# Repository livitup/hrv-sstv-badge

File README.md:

# DEFCON SSTV Badge

An open-source SSTV (Slow Scan Television) badge designed for DEFCON and the broader badgelife community. This badge combines amateur radio, digital imaging, and social interaction into a wearable electronic art piece shaped like a Simpsons-style retro TV with rabbit ear antennas.

## Project Overview

The DEFCON SSTV Badge enables users to:
- **Capture photos** with an integrated 2MP OV2640 camera
- **Encode images** into SSTV format with callsign overlay
- **Transmit images** via VHF/UHF radio using the SA818 transceiver
- **Receive SSTV signals** from other badges and stations
- **Store and browse** images on microSD card
- **Interact socially** through visual radio communication

Perfect for ham radio operators, makers, and anyone interested in digital modes and RF experimentation.

## Features

### Hardware Capabilities
- **RP2350B Dual-Core MCU** - QFN-80, 48 GPIOs, dedicated cores for UI and signal processing
- **SA818 VHF/UHF Transceiver** - 1W output on swappable carrier board (see below)
- **OV2640 2MP Camera** - Parallel DVP interface with 15-20 FPS live viewfinder via PIO
- **2.4" ILI9341 TFT Display** - 320x240 landscape, SPI interface
- **PCM5102A DAC + RP2350 ADC** - I2S DAC for TX audio, internal ADC for RX audio
- **MicroSD Storage** - Standalone SD socket (J10), shared SPI bus with display
- **2000mAh LiPo Battery** - 8-10 hours operation with USB-C charging
- **2x SAO Connectors** - Standard Shitty Add-On expansion ports
- **26x WS2812B LEDs** - Animated blinky chain across rabbit ears and display border

### Radio Features
- **Dual-Band Support** - VHF (134-174 MHz) and UHF (400-480 MHz) via carrier board swap
- **Multiple SSTV Modes** - Martin, Scottie, Robot modes with auto-detection
- **Automatic Operation** - No manual PTT required
- **Airplane Mode** - Physical slide switch to disable RF
- **SMA Antenna Port** - On carrier board, right-angle connector with antenna pointing up

### User Interface
- **5-Way D-Pad** - Navigation, menu selection, and photo capture (center button doubles as shutter)
- **Airplane Mode Switch** - Slide switch for RF enable/disable
- **PWR LED** - Traditional RGB LED for battery and system status
- **Blinky LEDs** - 26x WS2812B chain with animated TX/RX/idle patterns
- **Customizable Settings** - Callsign, frequency, SSTV mode, and more

## SA818 Carrier Board System

The SA818 transceiver has 2mm pitch castellated pads that are incompatible with user-swappable sockets. Instead of mounting the SA818 directly on the main badge, the design uses a full-width carrier board system.

### How It Works

The carrier board is a separate PCB (full badge width, ~120mm) that overlays the top portion of the main badge. The SA818 module, SMA connector, and antenna are ALL on the carrier board -- the main badge has zero RF traces.

**Mounting:** 4-point connection via 2x 1x8 signal headers (bottom edge) + 2x 1x3 mechanical headers (top corners, grounded for RF shielding).

**Band detection:** Each carrier has an ID resistor (0 ohm for VHF, DNP for UHF) read by the RP2350B on startup. The firmware automatically detects which carrier is installed and configures frequency limits accordingly. No DIP switches or manual configuration needed.

### Carrier Variants

- **SA818-V Carrier** - VHF (134-174 MHz) with matched VHF stubby antenna
- **SA818-U Carrier** - UHF (400-480 MHz) with matched UHF stubby antenna

### Swapping Carriers

1. Power down the badge
2. Unplug the current carrier board from the headers
3. Plug in the replacement carrier (VHF or UHF)
4. Power on -- firmware auto-detects the band and configures itself

Each carrier includes a band-matched stubby antenna, so users do not need to source separate antennas.

### Design Benefits

- Main badge PCB has no RF routing, simplifying layout and potentially enabling 2-layer PCB
- Carrier board has proper 50-ohm microstrip trace from SA818 to SMA
- Ground stitching around RF trace on carrier for shielding
- SA818 is factory-assembled onto carrier (2mm pitch not user-solderable)

## Power System

The SA818 draws up to 1.7A during TX, which would overwhelm a standard 3.3V regulator. The power system separates the radio from the digital rail:

```
LiPo (3.0-4.2V) --+---> TPS63001 (buck-boost) ---> 3.3V Rail (RP2350B, display, camera, etc.)
                   |
                   +---> TPS22919 (load switch) ---> SA818 (3.5-5.5V direct from LiPo)
```

- **TPS63001**: Buck-boost regulator, 3.3V output, handles full LiPo voltage range (3.0-4.2V)
- **TPS22919**: Load switch controls SA818 power (enables airplane mode and sleep)
- **MCP73871**: Battery charging controller with USB-C input
- **LC709203F**: Battery fuel gauge (I2C)

## Amateur Radio License Verification System

To comply with FCC Part 97 regulations, the badge includes a software-based license verification system.

### Operating Modes

- **Receive-Only Mode**: Default for unlicensed users. Can receive and decode SSTV images but cannot transmit.
- **Licensed Mode**: Full TX/RX for verified amateur radio operators.

### Verification Process

During initial setup, users enter their amateur radio callsign. The badge generates a unique unlock code from the callsign and the device's hardware serial number using SHA-256 hashing. This ensures each unlock code is specific to one badge-callsign combination, preventing casual code sharing between devices.

Licensed operators get full transmit capability with automatic callsign overlay on transmitted images (FCC requirement). Unlicensed users can still receive and view SSTV images -- all reception features work normally.

This system encourages proper amateur radio operation. It is not intended as absolute copy protection.

## Project Status

**Current Phase: PCB Layout**

| Milestone | Status |
|-----------|--------|
| System architecture and block diagram | Complete |
| Schematic design (all sheets) | Complete, ERC clean |
| KiCad schematic entry | Complete (all sheets) |
| SA818 carrier board PCBs (VHF + UHF) | Complete |
| Bill of materials and sourcing | Complete |
| Main badge PCB layout | In progress |
| Firmware development | Not started |
| Prototype assembly and testing | Pending PCB fabrication |

## Repository Structure

```
hrv-sstv-badge/
├── CLAUDE.md                       # AI context file (project specs)
├── CMakeLists.txt                  # Build system
├── CONTRIBUTING.md                 # Contribution guidelines
├── LICENSE                         # MIT license
├── README.md                       # This file
├── docs/                           # Documentation
│   ├── block-diagram.png           # System overview diagram
│   ├── electrical-design.md        # Circuit schematics and component specs
│   ├── firmware-architecture.md    # Detailed software design
│   ├── bom.md                      # Bill of materials with costs
│   ├── bom-raw.md                  # Raw BOM data
│   ├── project-status.md           # Design status tracker
│   └── engineers-notebook/         # Design decisions and rationale
├── firmware/                       # RP2350B embedded firmware (not yet started)
├── hardware/                       # KiCad PCB design files
│   ├── main_badge/                 # Main badge KiCad project
│   ├── sa818-v-carrier/            # VHF carrier board KiCad project
│   ├── sa818-u-carrier/            # UHF carrier board KiCad project
│   ├── footprints.pretty/          # Custom KiCad footprints
│   ├── symbols/                    # Custom KiCad symbols
│   ├── pcb-design.md               # PCB layout guidelines
│   └── README.md                   # Hardware design notes
├── mechanical/                     # Badge accessories and mounting
└── src/                            # Source scaffolding
```

## Technical Specifications

| Parameter | Specification |
|-----------|---------------|
| **MCU** | Raspberry Pi RP2350B (QFN-80), Dual ARM Cortex-M33 |
| **Radio** | SA818 VHF/UHF on carrier board, 1W output |
| **Frequency Range** | VHF: 134-174 MHz, UHF: 400-480 MHz |
| **Camera** | OV2640, 2MP, parallel DVP (8-bit), QVGA for SSTV |
| **Display** | 2.4" ILI9341 TFT LCD, 320x240 landscape, SPI |
| **Audio TX** | PCM5102A DAC via I2S |
| **Audio RX** | RP2350B internal ADC with anti-alias filter |
| **Storage** | MicroSD via standalone SD socket J10 (shared SPI bus) |
| **Battery** | 2000mAh LiPo, USB-C charging (MCP73871) |
| **Regulator** | TPS63001 buck-boost, 3.3V output |
| **Operating Time** | 8-10 hours typical use |
| **LEDs** | 26x WS2812B (10x 5050 on ears, 16x 2020 on border) + RGB PWR LED |
| **Expansion** | 2x SAO (Shitty Add-On) connectors |
| **Dimensions** | ~120mm x 120mm body, ~190mm total height with ears and feet |
| **Form Factor** | Retro TV shape with rabbit ear antennas, wearable badge (no enclosure) |

## Software Architecture

The firmware uses a bare-metal dual-core design on the RP2350B for deterministic SSTV timing:

- **Core 0**: User interface, file system, system management, display updates
- **Core 1**: SSTV encoding/decoding, audio DSP, camera control, radio management

PIO state machines handle hardware-timed signals (camera capture, WS2812B data, audio clocking). DMA transfers move data without CPU intervention. No RTOS -- bare metal for microsecond-precision SSTV timing.

### Development Environment
- **Language**: C11 (ISO/IEC 9899:2011)
- **Compiler**: GCC ARM Embedded (arm-none-eabi-gcc)
- **Build System**: CMake with Raspberry Pi Pico SDK
- **Debugger**: OpenOCD + GDB via SWD (Tag-Connect)

## Assembly Model

This badge uses a production kit approach:

- **Factory-assembled**: All SMD components on main badge, SA818 onto carrier boards
- **User-assembled at conference**: Through-hole parts (switches, connectors, pin headers)
- **User-configured**: Plug in VHF or UHF carrier board, insert battery, insert SD card

## Getting Started

### Prerequisites
- **Amateur Radio License** - Required for transmit operation (receive works without)
- **Basic Soldering Skills** - Through-hole soldering for final assembly

### Firmware Installation
1. Download the latest firmware release
2. Connect via USB-C while holding BOOTSEL
3. Copy the UF2 file to the mounted drive
4. Configure callsign, frequency, and SSTV mode

### Build from Source
```bash
mkdir build && cd build
cmake .. -DCMAKE_BUILD_TYPE=Debug
make -j4

# Flash via UF2 bootloader
cp defcon_sstv_badge.uf2 /Volumes/RPI-RP2/

# Or flash via SWD
openocd -f interface/cmsis-dap.cfg -f target/rp2350.cfg
```

## Badgelife Integration

- **SAO Compatibility** - 2x standard Shitty Add-On connectors (I2C + 2 GPIOs each)
- **Badge-to-Badge Communication** - SSTV image exchange over the air
- **Retro TV Aesthetic** - PCB shaped like a classic TV with rabbit ear antennas
- **Animated LEDs** - 26 WS2812B LEDs with TX/RX/idle animations across ears and display border
- **Open Source** - Hardware and software fully open for hacking and modification

## Legal and Compliance

### Amateur Radio Requirements
- Valid amateur radio license required for transmit operation
- Operate only within licensed frequency allocations
- Follow local RF exposure and power limitations
- Respect band plans and operating procedures

### Regulatory
- FCC Part 97 (United States)
- IC RSS (Canada)
- CE marking (Europe)
- Consult local regulations for other countries

### Safety
- RF radiation exposure -- use appropriate antenna and power levels
- LiPo battery safety -- follow proper charging and storage procedures
- ESD precautions during assembly

## Contributing

Contributions from the badgelife and amateur radio communities are welcome.

### How to Contribute
- **Report Issues** - Found a bug? Open a GitHub issue
- **Submit Pull Requests** - Code improvements, documentation fixes
- **Share Ideas** - Feature requests and enhancement suggestions
- **Test Hardware** - Help validate designs and assembly procedures

### Development Areas
- **Hardware**: PCB layout, carrier board design
- **Firmware**: SSTV algorithms, UI, power management
- **Documentation**: Assembly guides, user manuals, tutorials

## License

- **Hardware**: [CERN-OHL-S v2](https://cern-ohl.web.cern.ch/)
- **Software**: [MIT License](LICENSE)
- **Documentation**: [CC BY-SA 4.0](https://creativecommons.org/licenses/by-sa/4.0/)

## Support and Community

- **Documentation** - See the `docs/` directory
- **Issues** - Open a GitHub issue for bugs or questions
- **Discussions** - Use GitHub Discussions for general topics
- **DEFCON** - Hardware Hacking Village and Ham Radio Village

---

**Made for the badgelife and amateur radio communities. See you at DEFCON!**

**73s!**

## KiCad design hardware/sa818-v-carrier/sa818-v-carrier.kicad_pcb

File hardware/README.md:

# DEFCON SSTV Badge — Hardware Design

This directory contains all KiCad design files for the DEFCON SSTV Badge.

## Directory Structure

```
hardware/
├── main_badge/                    # Main badge KiCad project
│   ├── defcon-sstv-badge.kicad_pro    # Project file
│   ├── defcon-sstv-badge.kicad_sch    # Top-level schematic
│   ├── defcon-sstv-badge.kicad_pcb    # PCB layout (in progress)
│   ├── power.kicad_sch                # Power: TPS63001, TPS22919, MCP73871, LC709203F
│   ├── audio.kicad_sch                # Audio: PCM5102A DAC, TX/RX filters
│   ├── camera-display.kicad_sch       # Display (ILI9341) + Camera (OV2640)
│   ├── mcu.kicad_sch                  # RP2350B, crystal, flash, USB-C
│   ├── switches.kicad_sch             # D-pad, airplane switch, PWR LED, WS2812B chain
│   └── connectors.kicad_sch           # SAO×2, carrier headers, SD card, Tag-Connect
├── sa818-v-carrier/               # VHF carrier board (134-174 MHz)
│   ├── sa818-v-carrier.kicad_pro
│   ├── sa818-v-carrier.kicad_sch
│   └── sa818-v-carrier.kicad_pcb      # PCB layout complete
├── sa818-u-carrier/               # UHF carrier board (400-480 MHz)
│   ├── sa818-u-carrier.kicad_pro
│   ├── sa818-u-carrier.kicad_sch
│   └── sa818-u-carrier.kicad_pcb      # PCB layout complete
├── symbols/                       # Custom KiCad symbol libraries
├── footprints.pretty/             # Custom KiCad footprint libraries
├── fp-lib-table                   # Footprint library table
├── sym-lib-table                  # Symbol library table
├── pcb-design.md                  # PCB outline, dimensions, and layout zones
└── README.md                      # This file
```

## Design Overview

### Main Badge
- **PCB shape**: Simpsons-style retro TV with rabbit ear antennas and stubby feet
- **Body dimensions**: 120mm × 120mm
- **Total height**: ~190mm (ears + body + feet)
- **Layer count**: Targeting 4-layer (signal/ground/power/signal)
- **Thickness**: 1.6mm standard FR4
- **Soldermask**: Purple with white silkscreen (Simpsons TV aesthetic)

### Carrier Boards
- **Size**: Full badge width (~120mm), overlays top of main badge
- **Purpose**: SA818 module + SMA connector + antenna — all RF on carrier, none on main badge
- **Variants**: VHF (SA818-V) and UHF (SA818-U), identical PCB with different module population
- **PCB layout**: Complete for both variants

### Key Design Decisions
- **No RF on main badge** — all RF routing is on the carrier board
- **Carrier is front-mounted** — overlays the top portion of the main badge, top edges flush
- **4-point mounting** — 2× 1×8 signal headers + 2× 1×3 mechanical headers (GND for RF shielding)
- **Band auto-detect** — carrier ID resistor (0Ω = VHF, DNP = UHF) read by firmware on startup

## KiCad Version

This project uses **KiCad 8**. Custom symbols and footprints are included in the repository.

## Schematic Status

All schematic sheets are complete and ERC clean:
- Power, Audio, Display/Camera, MCU, Switches, Connectors (main badge)
- SA818-V Carrier, SA818-U Carrier

## PCB Layout Status

- **Carrier boards**: Complete (VHF and UHF)
- **Main badge**: Board outline complete (TV shape with ears and feet), component placement and routing in progress

## Related Documentation

- [PCB Design](pcb-design.md) — Board outline, dimensions, component placement zones
- [Electrical Design](../docs/electrical-design.md) — Circuit schematics and component specs
- [BOM](../docs/bom.md) — Bill of materials with costs and sourcing
- [Project Status](../docs/project-status.md) — Design and implementation tracker

---

*73 de HRV*

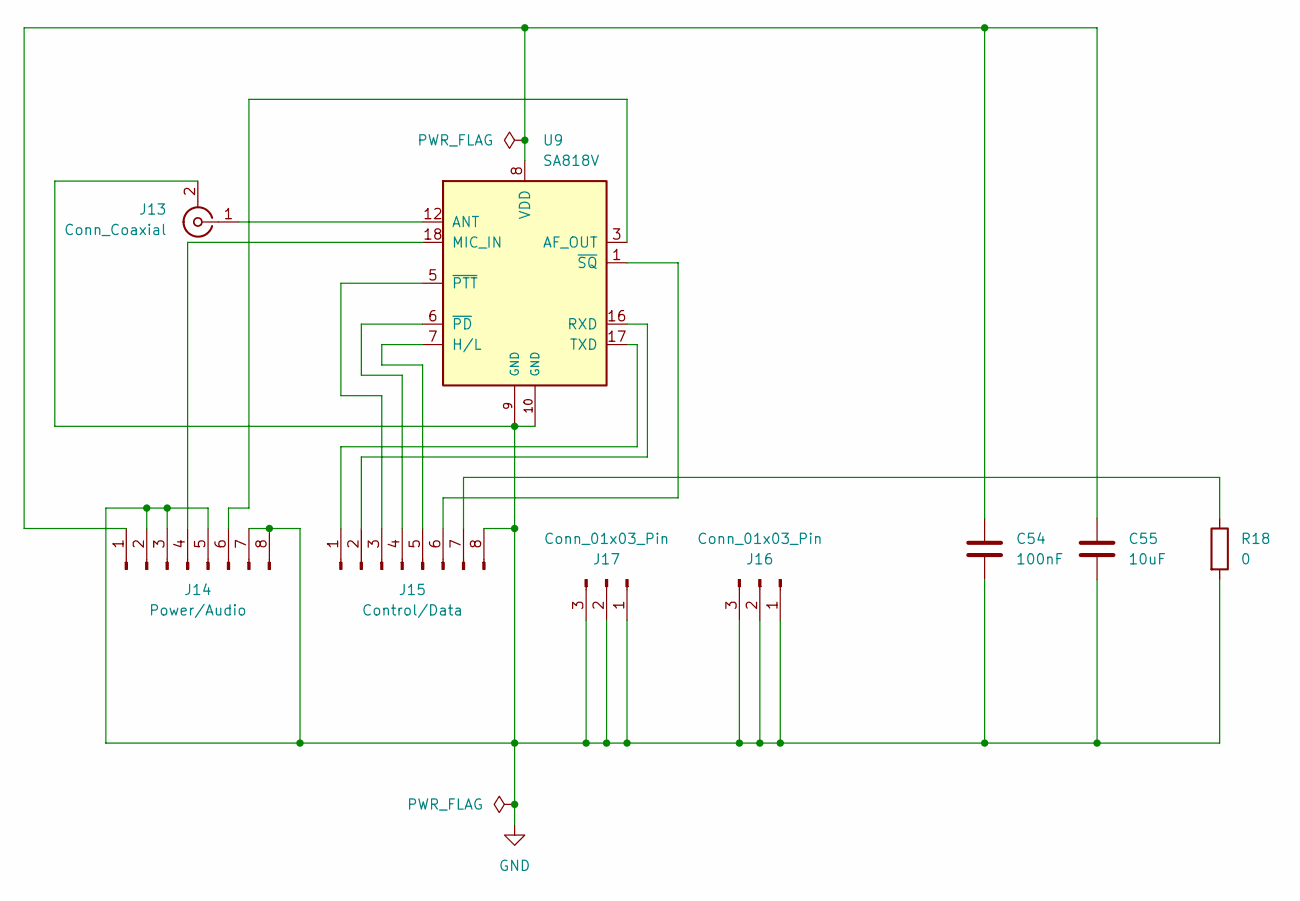
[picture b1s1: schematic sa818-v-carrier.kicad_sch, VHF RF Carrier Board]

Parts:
C54: 100nF; C_0402_1005Metric
C55: 10uF; C_0603_1608Metric
J13: Conn_Coaxial; SMA_Amphenol_132289_EdgeMount
J14: Power/Audio; PinHeader_1x08_P2.54mm_Vertical
J15: Control/Data; PinHeader_1x08_P2.54mm_Vertical
J16, J17: Conn_01x03_Pin; PinHeader_1x03_P2.54mm_Vertical
R18: 0; R_0402_1005Metric
U9: SA818V; VHF_UHF_Module_generic

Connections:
GND: C54.2, C55.2, J13.2 (Ext), J14.2, J14.3, J14.5, J14.7, J14.8, J15.8, J16.1, J16.2, J16.3, J17.1, J17.2, J17.3, R18.2, U9.9 (GND), U9.10 (GND)
unnamed: J13.1 (In), U9.12 (ANT)
unnamed: C54.1, C55.1, J14.1, U9.8 (VDD)
unnamed: J14.4, U9.18 (MIC_IN)
unnamed: J14.6, U9.3 (AF_OUT)
unnamed: J15.1, U9.17 (TXD)
unnamed: J15.2, U9.16 (RXD)
unnamed: J15.3, U9.5 (~PTT)
unnamed: J15.4, U9.6 (~PD)
unnamed: J15.5, U9.7 (H/L)
unnamed: J15.6, U9.1 (~SQ)
unnamed: J15.7, R18.1

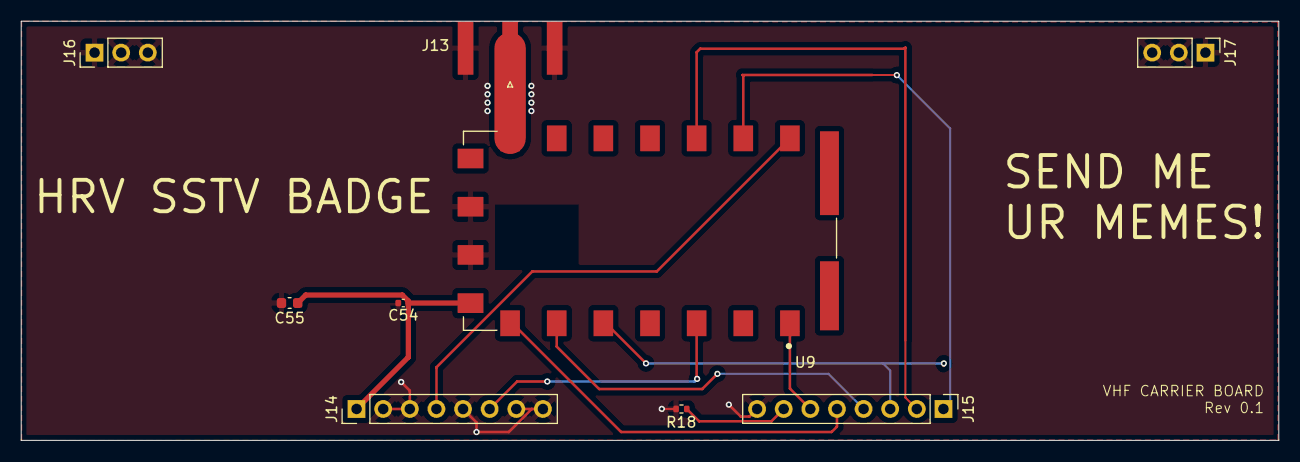
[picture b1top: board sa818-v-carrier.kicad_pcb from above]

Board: 2 copper layers, 120.0 x 40.0 mm, 9 parts (0 on the bottom side), 12 nets.

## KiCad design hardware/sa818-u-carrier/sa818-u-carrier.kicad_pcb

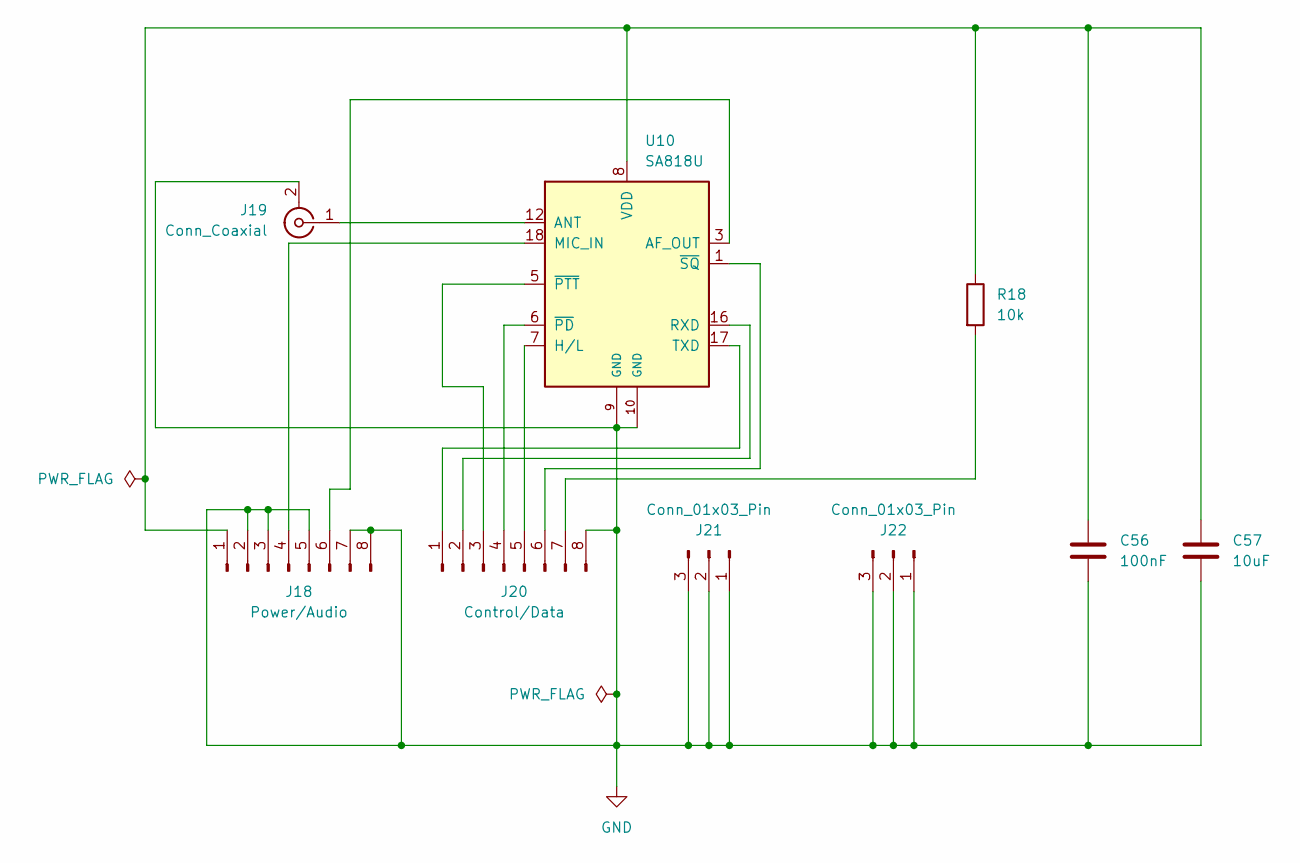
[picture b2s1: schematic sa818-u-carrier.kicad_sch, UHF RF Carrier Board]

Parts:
C56: 100nF; C_0402_1005Metric
C57: 10uF; C_0603_1608Metric
J18: Power/Audio; PinHeader_1x08_P2.54mm_Vertical
J19: Conn_Coaxial; SMA_Amphenol_132289_EdgeMount
J20: Control/Data; PinHeader_1x08_P2.54mm_Vertical
J21, J22: Conn_01x03_Pin; PinHeader_1x03_P2.54mm_Vertical
R18: 10k; R_0402_1005Metric
U10: SA818U; VHF_UHF_Module_generic

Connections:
GND: C56.2, C57.2, J18.2, J18.3, J18.5, J18.7, J18.8, J19.2 (Ext), J20.8, J21.1, J21.2, J21.3, J22.1, J22.2, J22.3, U10.9 (GND), U10.10 (GND)
unnamed: C56.1, C57.1, J18.1, R18.1, U10.8 (VDD)
unnamed: J18.4, U10.18 (MIC_IN)
unnamed: J18.6, U10.3 (AF_OUT)
unnamed: J19.1 (In), U10.12 (ANT)
unnamed: J20.1, U10.17 (TXD)
unnamed: J20.2, U10.16 (RXD)
unnamed: J20.3, U10.5 (~PTT)
unnamed: J20.4, U10.6 (~PD)
unnamed: J20.5, U10.7 (H/L)
unnamed: J20.6, U10.1 (~SQ)
unnamed: J20.7, R18.2

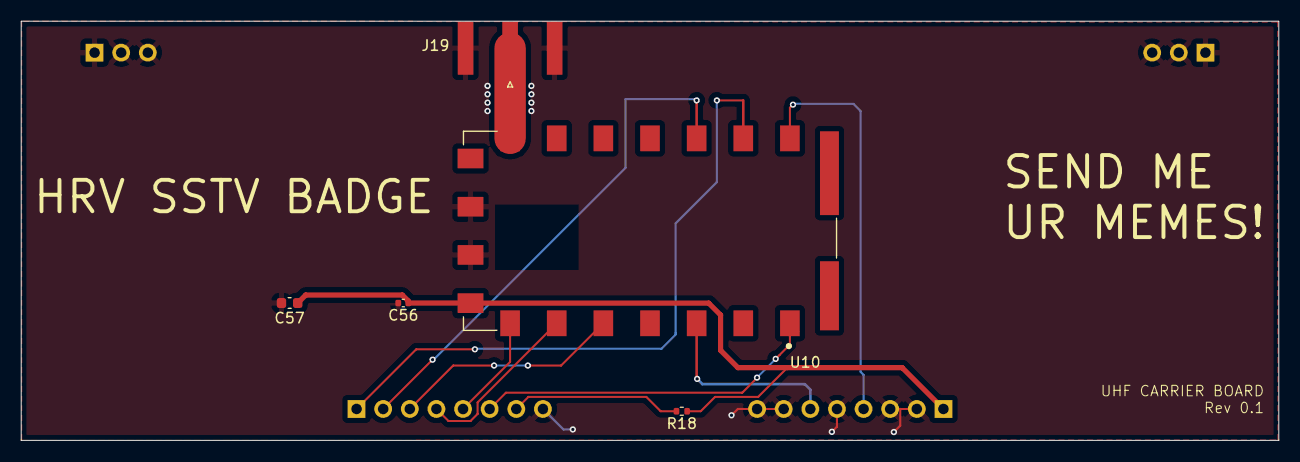
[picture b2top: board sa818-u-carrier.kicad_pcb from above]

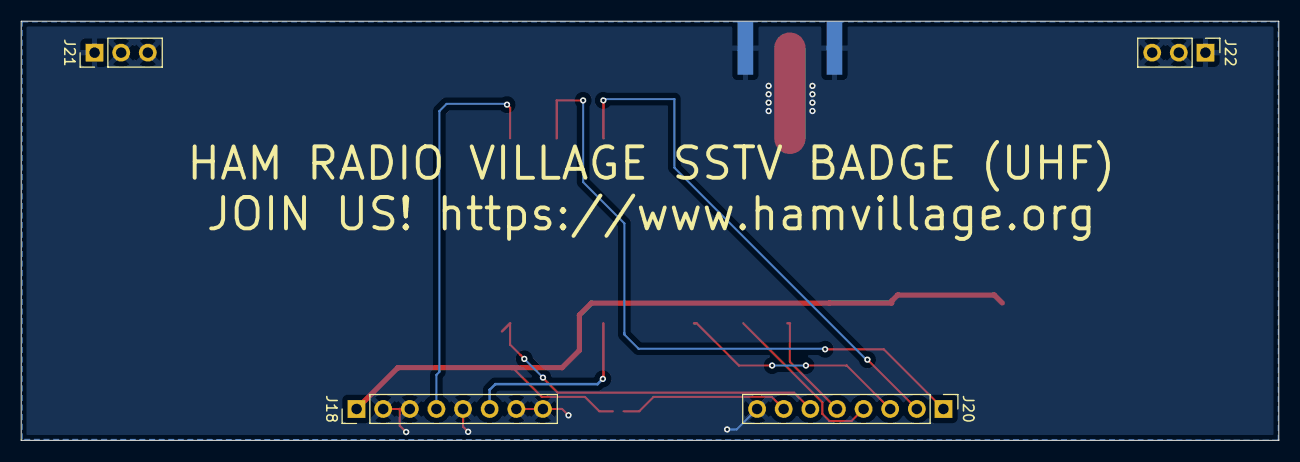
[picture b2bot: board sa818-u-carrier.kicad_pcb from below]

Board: 2 copper layers, 120.0 x 40.0 mm, 9 parts (4 on the bottom side), 12 nets.

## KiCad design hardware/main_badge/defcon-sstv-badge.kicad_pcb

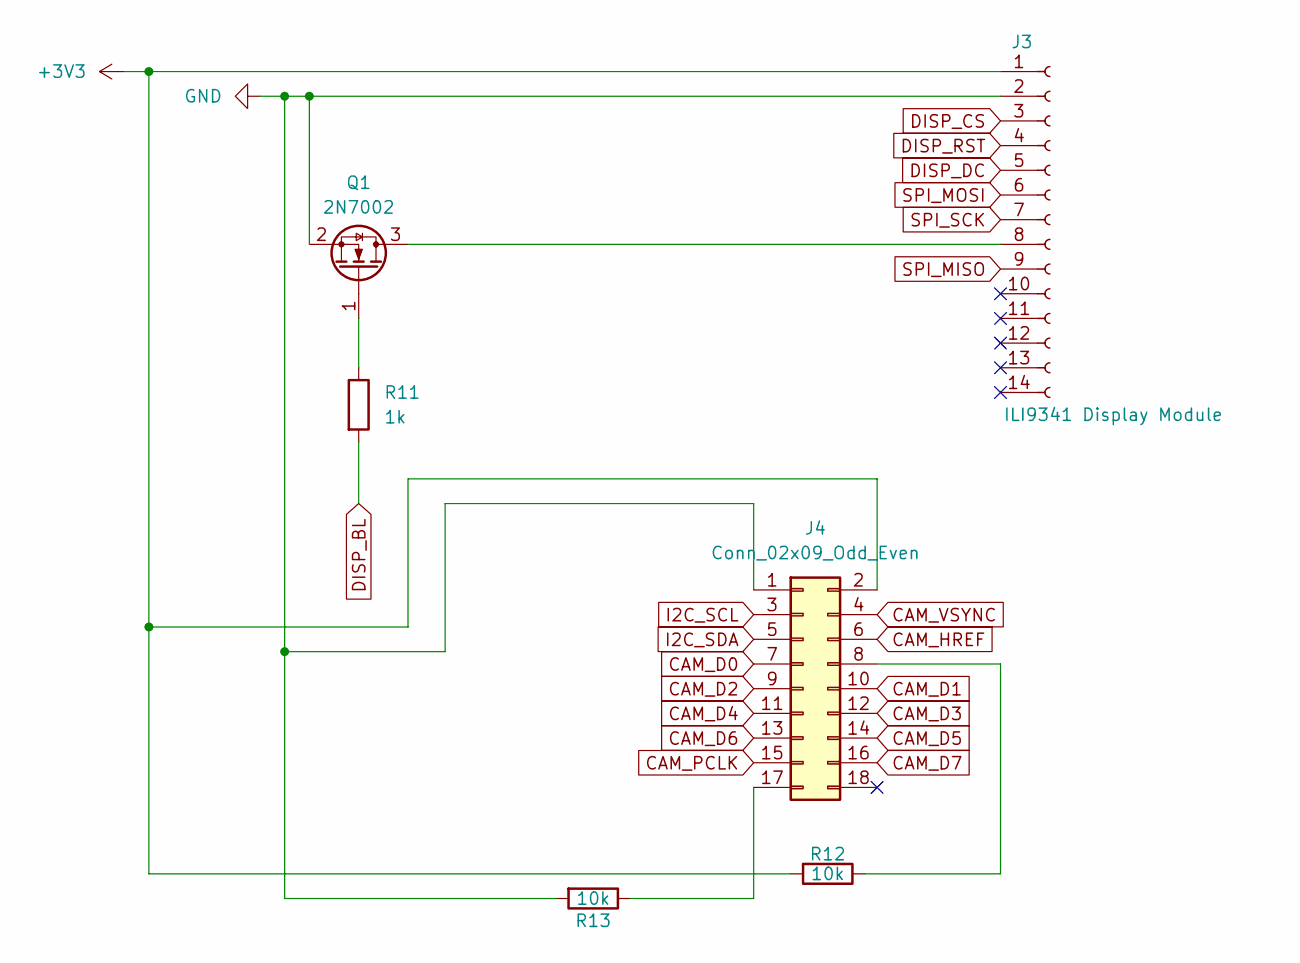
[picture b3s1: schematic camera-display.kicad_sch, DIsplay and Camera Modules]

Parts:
J3: ILI9341 Display Module; PinSocket_1x14_P2.54mm_Vertical
J4: Conn_02x09_Odd_Even; PinSocket_2x09_P2.54mm_Vertical
Q1: 2N7002; SOT-23
R11: 1k; R_0603_1608Metric
R12, R13: 10k; R_0603_1608Metric

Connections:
+3V3: J3.1, J4.2, R12.2; also elsewhere on the board
CAM_D0: J4.7; also elsewhere on the board
CAM_D1: J4.10; also elsewhere on the board
CAM_D2: J4.9; also elsewhere on the board
CAM_D3: J4.12; also elsewhere on the board
CAM_D4: J4.11; also elsewhere on the board
CAM_D5: J4.14; also elsewhere on the board
CAM_D6: J4.13; also elsewhere on the board
CAM_D7: J4.16; also elsewhere on the board
CAM_HREF: J4.6; also elsewhere on the board
CAM_PCLK: J4.15; also elsewhere on the board
CAM_VSYNC: J4.4; also elsewhere on the board
DISP_BL: R11.2; also elsewhere on the board
DISP_CS: J3.3; also elsewhere on the board
DISP_DC: J3.5; also elsewhere on the board
DISP_RST: J3.4; also elsewhere on the board
I2C_SCL: J4.3; also elsewhere on the board
I2C_SDA: J4.5; also elsewhere on the board
unnamed: J3.8, Q1.3 (D)
unnamed: J4.8, R12.1
unnamed: J4.17, R13.1
unnamed: Q1.1 (G), R11.1
SPI_MISO: J3.9; also elsewhere on the board
SPI_MOSI: J3.6; also elsewhere on the board
SPI_SCK: J3.7; also elsewhere on the board

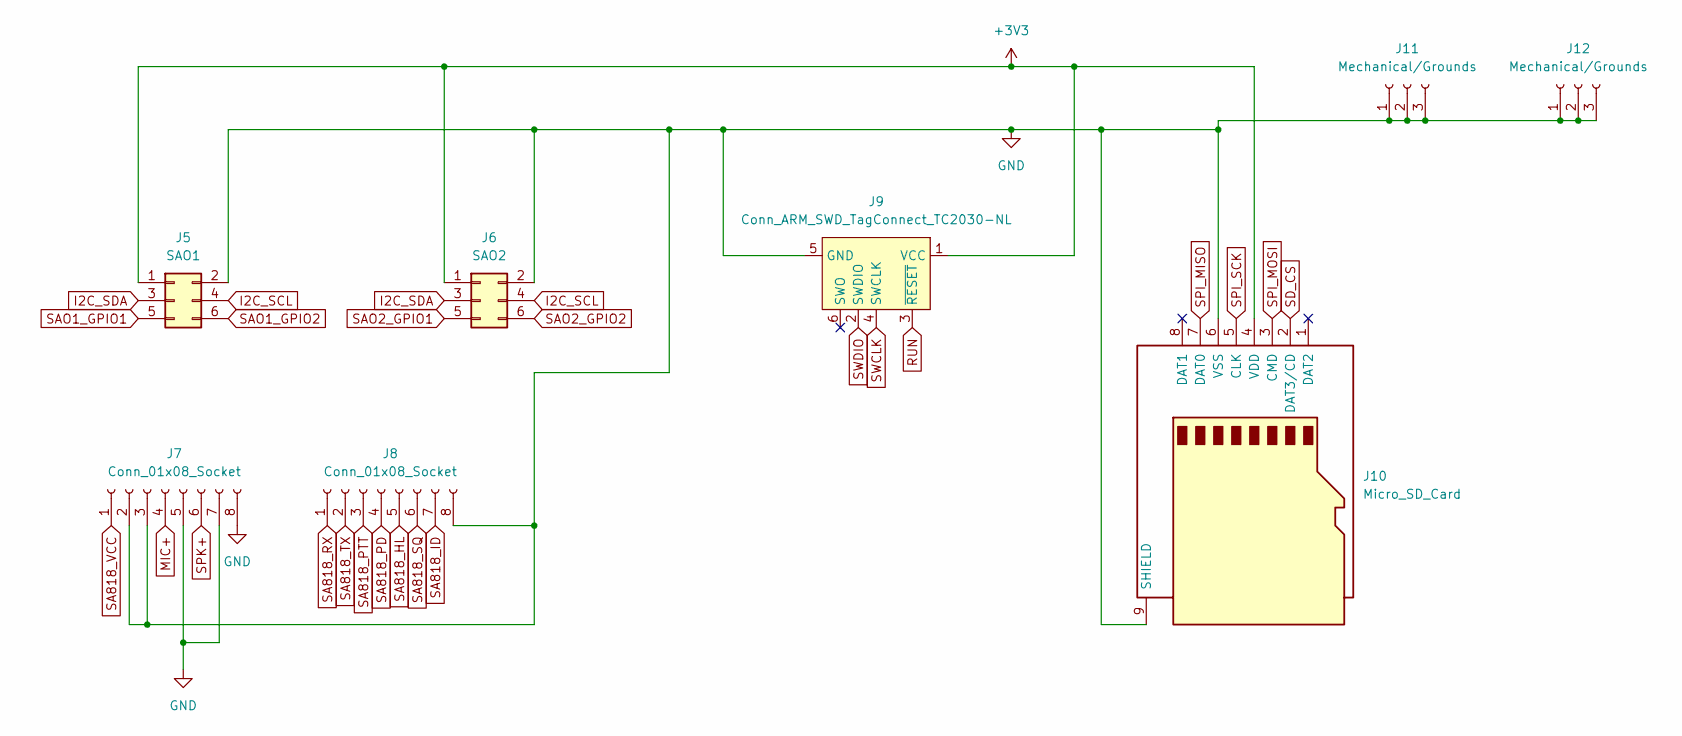
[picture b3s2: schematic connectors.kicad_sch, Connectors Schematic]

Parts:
J5: SAO1; PinHeader_2x03_P2.54mm_Vertical
J6: SAO2; PinHeader_2x03_P2.54mm_Vertical
J7, J8: Conn_01x08_Socket; PinSocket_1x08_P2.54mm_Vertical
J9: Conn_ARM_SWD_TagConnect_TC2030-NL; Tag-Connect_TC2030-IDC-NL_2x03_P1.27mm_Vertical
J10: Micro_SD_Card; microSD_HC_Molex_104031-0811
J11, J12: Mechanical/Grounds; PinSocket_1x03_P2.54mm_Vertical

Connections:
+3V3: J5.1, J6.1, J9.1 (VCC), J10.4 (VDD); also elsewhere on the board
I2C_SCL: J5.4, J6.4; also elsewhere on the board
I2C_SDA: J5.3, J6.3; also elsewhere on the board
MIC+: J7.4; also elsewhere on the board
RUN: J9.3 (~RESET); also elsewhere on the board
SA818_HL: J8.5; also elsewhere on the board
SA818_ID: J8.7; also elsewhere on the board
SA818_PD: J8.4; also elsewhere on the board
SA818_PTT: J8.3; also elsewhere on the board
SA818_RX: J8.1; also elsewhere on the board
SA818_SQ: J8.6; also elsewhere on the board
SA818_TX: J8.2; also elsewhere on the board
SA818_VCC: J7.1; also elsewhere on the board
SAO1_GPIO1: J5.5; also elsewhere on the board
SAO1_GPIO2: J5.6; also elsewhere on the board
SAO2_GPIO1: J6.5; also elsewhere on the board
SAO2_GPIO2: J6.6; also elsewhere on the board
SD_CS: J10.2 (DAT3/CD); also elsewhere on the board
SPI_MISO: J10.7 (DAT0); also elsewhere on the board
SPI_MOSI: J10.3 (CMD); also elsewhere on the board
SPI_SCK: J10.5 (CLK); also elsewhere on the board
SPK+: J7.6; also elsewhere on the board
SWCLK: J9.4 (SWCLK); also elsewhere on the board
SWDIO: J9.2 (SWDIO); also elsewhere on the board

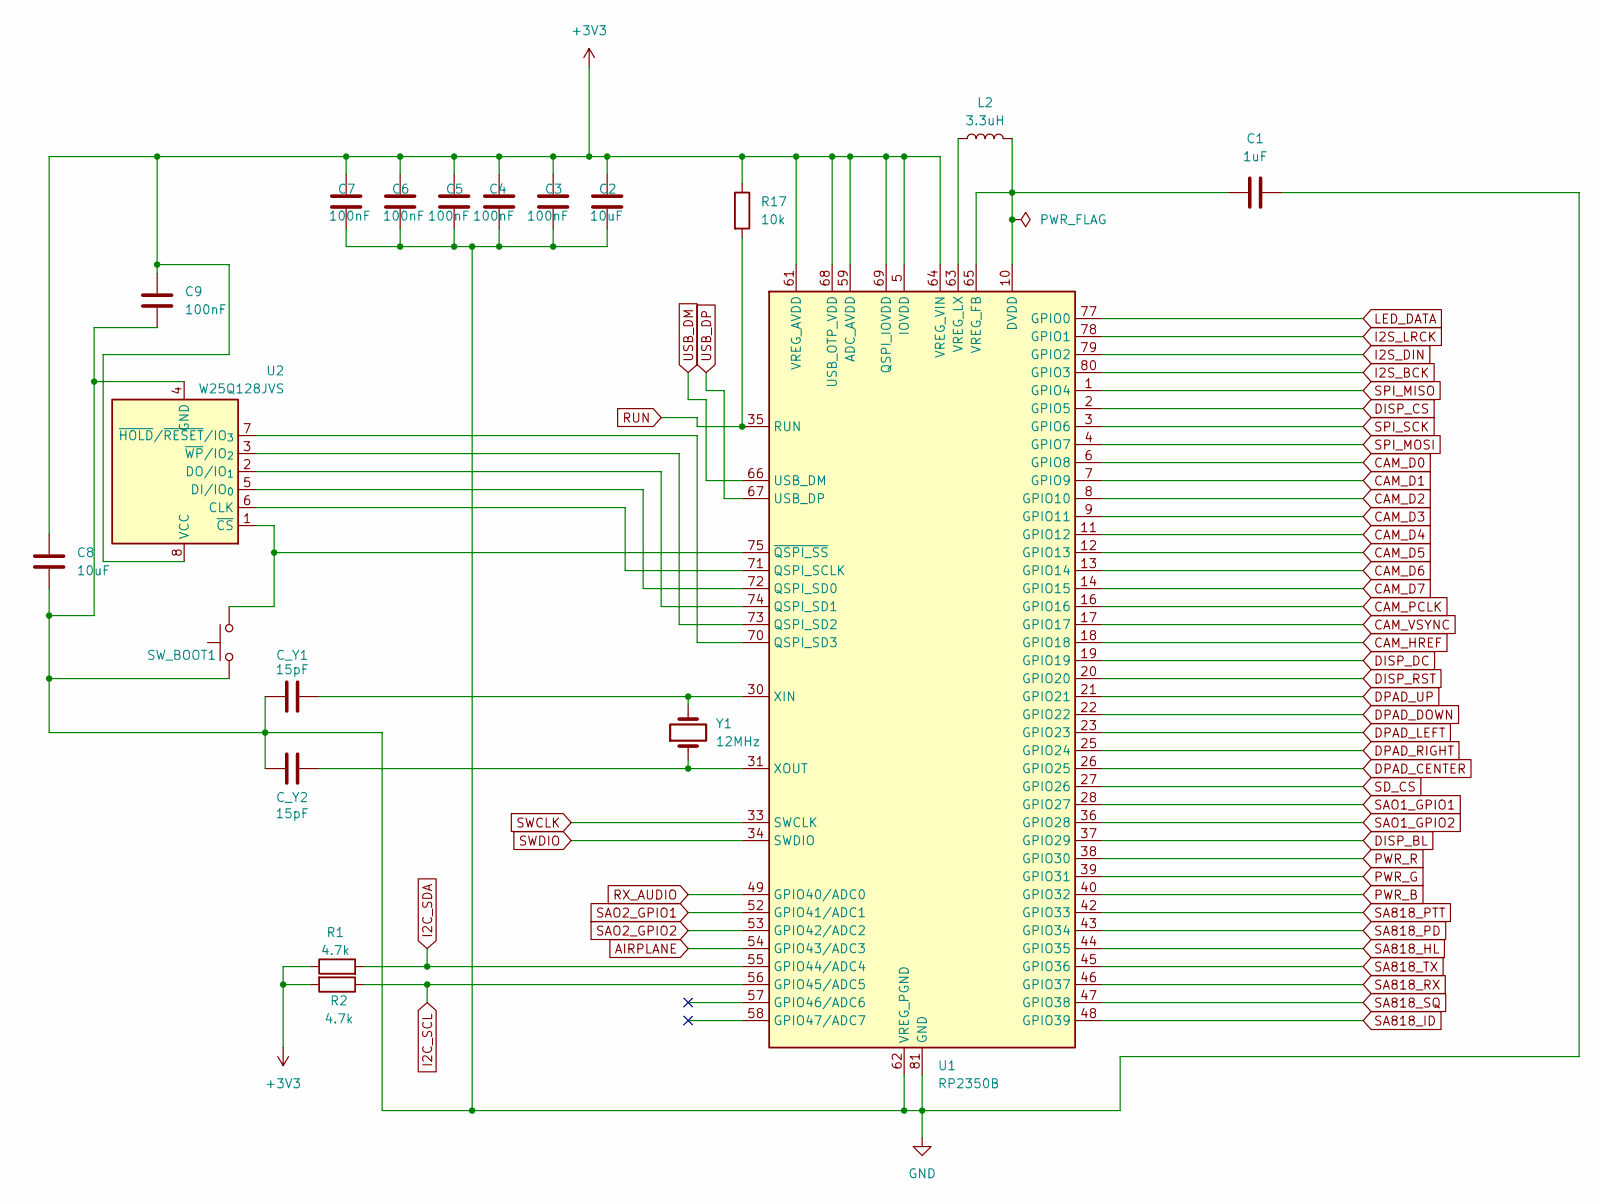
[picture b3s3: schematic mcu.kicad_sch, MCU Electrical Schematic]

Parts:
C1: 1uF; C_0402_1005Metric
C2: 10uF; C_0603_1608Metric
C3, C4, C5, C6, C7, C9: 100nF; C_0402_1005Metric
C8: 10uF; C_0805_2012Metric
C_Y1, C_Y2: 15pF; C_0402_1005Metric
L2: 3.3uH; L_Taiyo-Yuden_NR-30xx_HandSoldering
R1, R2: 4.7k; R_0603_1608Metric
R17: 10k; R_0603_1608Metric
SW_BOOT1: SW_Push; SW_SPST_CK_RS282G05A3
U1: RP2350B; QFN-80-1EP_10x10mm_P0.4mm_EP3.4x3.4mm
U2: W25Q128JVS; SOIC-8_5.3x5.3mm_P1.27mm
Y1: 12MHz; Crystal_SMD_3215-2Pin_3.2x1.5mm

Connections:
+3V3: C2.1, C3.1, C4.1, C5.1, C6.1, C7.1, C8.1, C9.1, R1.1, R2.2, R17.1, U1.5 (IOVDD), U1.15 (IOVDD), U1.24 (IOVDD), U1.29 (IOVDD), U1.41 (IOVDD), U1.50 (IOVDD), U1.59 (ADC_AVDD), U1.60 (IOVDD), U1.61 (VREG_AVDD), U1.64 (VREG_VIN), U1.68 (USB_OTP_VDD), U1.69 (QSPI_IOVDD), U1.76 (IOVDD), U2.8 (VCC); also elsewhere on the board
AIRPLANE: U1.54 (GPIO43/ADC3); also elsewhere on the board
CAM_D0: U1.6 (GPIO8); also elsewhere on the board
CAM_D1: U1.7 (GPIO9); also elsewhere on the board
CAM_D2: U1.8 (GPIO10); also elsewhere on the board
CAM_D3: U1.9 (GPIO11); also elsewhere on the board
CAM_D4: U1.11 (GPIO12); also elsewhere on the board
CAM_D5: U1.12 (GPIO13); also elsewhere on the board
CAM_D6: U1.13 (GPIO14); also elsewhere on the board
CAM_D7: U1.14 (GPIO15); also elsewhere on the board
CAM_HREF: U1.18 (GPIO18); also elsewhere on the board
CAM_PCLK: U1.16 (GPIO16); also elsewhere on the board
CAM_VSYNC: U1.17 (GPIO17); also elsewhere on the board
DISP_BL: U1.37 (GPIO29); also elsewhere on the board
DISP_CS: U1.2 (GPIO5); also elsewhere on the board
DISP_DC: U1.19 (GPIO19); also elsewhere on the board
DISP_RST: U1.20 (GPIO20); also elsewhere on the board
DPAD_CENTER: U1.26 (GPIO25); also elsewhere on the board
DPAD_DOWN: U1.22 (GPIO22); also elsewhere on the board
DPAD_LEFT: U1.23 (GPIO23); also elsewhere on the board
DPAD_RIGHT: U1.25 (GPIO24); also elsewhere on the board
DPAD_UP: U1.21 (GPIO21); also elsewhere on the board
I2C_SCL: R2.1, U1.56 (GPIO45/ADC5); also elsewhere on the board
I2C_SDA: R1.2, U1.55 (GPIO44/ADC4); also elsewhere on the board
I2S_BCK: U1.80 (GPIO3); also elsewhere on the board
I2S_DIN: U1.79 (GPIO2); also elsewhere on the board
I2S_LRCK: U1.78 (GPIO1); also elsewhere on the board
LED_DATA: U1.77 (GPIO0); also elsewhere on the board
unnamed: U1.71 (QSPI_SCLK), U2.6 (CLK)
unnamed: U1.72 (QSPI_SD0), U2.5 (DI/IO_{0})
unnamed: U1.74 (QSPI_SD1), U2.2 (DO/IO_{1})
unnamed: U1.73 (QSPI_SD2), U2.3 (~WP/IO_{2})
unnamed: U1.70 (QSPI_SD3), U2.7 (~HOLD/~RESET/IO_{3})
unnamed: C1.1, L2.2, U1.10 (DVDD), U1.32 (DVDD), U1.51 (DVDD), U1.65 (VREG_FB)
unnamed: L2.1, U1.63 (VREG_LX)
unnamed: C_Y1.2, U1.30 (XIN), Y1.2
unnamed: C_Y2.2, U1.31 (XOUT), Y1.1
unnamed: SW_BOOT1.2, U1.75 (~QSPI_SS), U2.1 (~CS)
PWR_B: U1.40 (GPIO32); also elsewhere on the board
PWR_G: U1.39 (GPIO31); also elsewhere on the board
PWR_R: U1.38 (GPIO30); also elsewhere on the board
RUN: R17.2, U1.35 (RUN); also elsewhere on the board
RX_AUDIO: U1.49 (GPIO40/ADC0); also elsewhere on the board
SA818_HL: U1.44 (GPIO35); also elsewhere on the board
SA818_ID: U1.48 (GPIO39); also elsewhere on the board
SA818_PD: U1.43 (GPIO34); also elsewhere on the board
SA818_PTT: U1.42 (GPIO33); also elsewhere on the board
SA818_RX: U1.46 (GPIO37); also elsewhere on the board
SA818_SQ: U1.47 (GPIO38); also elsewhere on the board
SA818_TX: U1.45 (GPIO36); also elsewhere on the board
SAO1_GPIO1: U1.28 (GPIO27); also elsewhere on the board
SAO1_GPIO2: U1.36 (GPIO28); also elsewhere on the board
SAO2_GPIO1: U1.52 (GPIO41/ADC1); also elsewhere on the board
SAO2_GPIO2: U1.53 (GPIO42/ADC2); also elsewhere on the board
SD_CS: U1.27 (GPIO26); also elsewhere on the board
SPI_MISO: U1.1 (GPIO4); also elsewhere on the board
SPI_MOSI: U1.4 (GPIO7); also elsewhere on the board
SPI_SCK: U1.3 (GPIO6); also elsewhere on the board
SWCLK: U1.33 (SWCLK); also elsewhere on the board
SWDIO: U1.34 (SWDIO); also elsewhere on the board
USB_DM: U1.66 (USB_DM); also elsewhere on the board
USB_DP: U1.67 (USB_DP); also elsewhere on the board

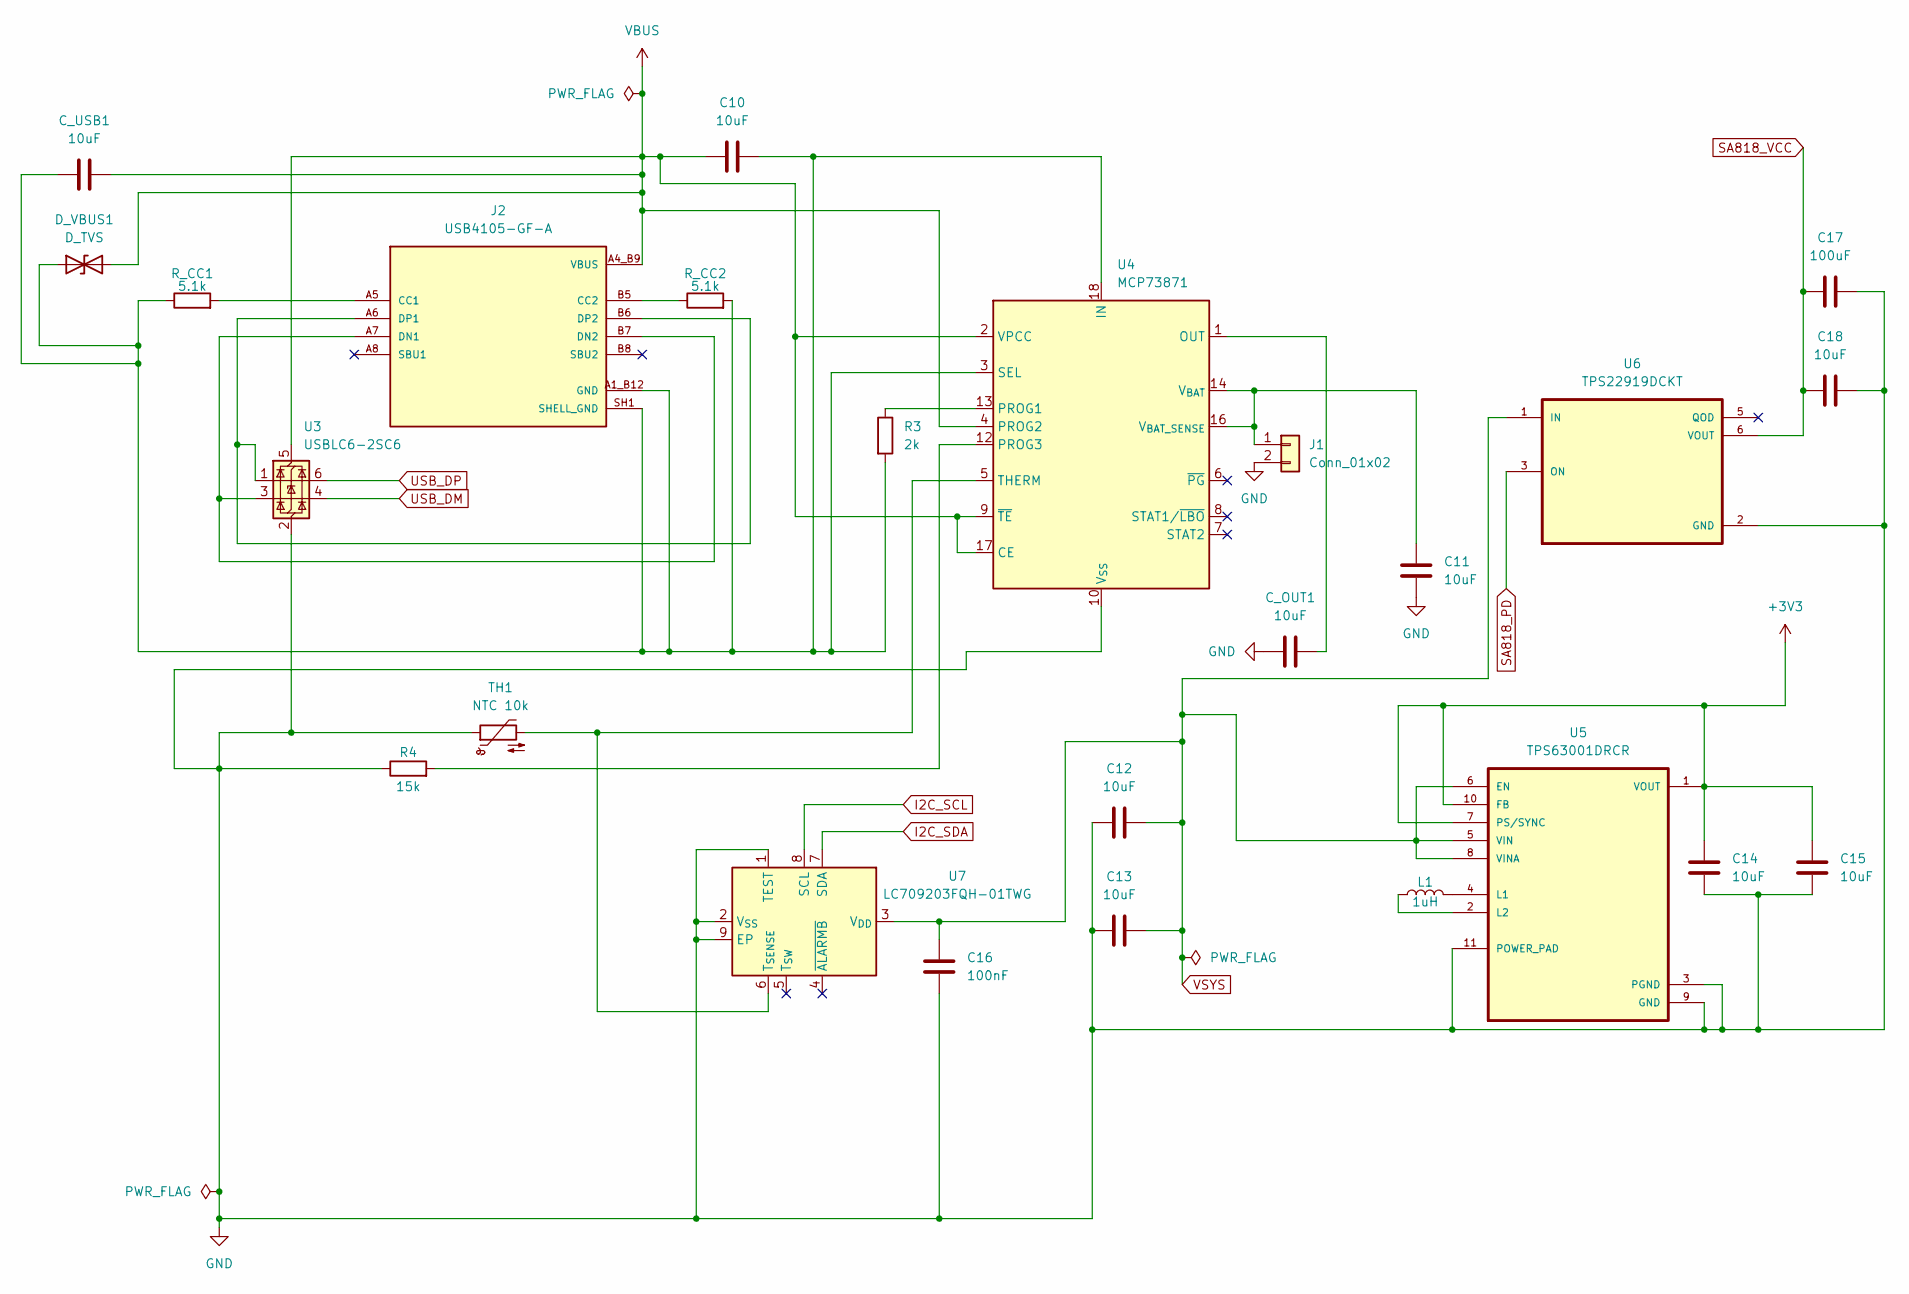
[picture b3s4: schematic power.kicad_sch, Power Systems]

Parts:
C10, C11, C12, C13, C14, C15: 10uF; C_0805_2012Metric
C16: 100nF; C_0402_1005Metric
C17: 100uF; C_1206_3216Metric
C18: 10uF; C_0603_1608Metric
C_OUT1: 10uF; C_0805_2012Metric
C_USB1: 10uF; C_0603_1608Metric
D_VBUS1: D_TVS; D_SOD-323
J1: Conn_01x02; JST_PH_B2B-PH-K_1x02_P2.00mm_Vertical
J2: USB4105-GF-A; GCT_USB4105-GF-A; PARTREV B4
L1: 1uH; L_Taiyo-Yuden_NR-30xx_HandSoldering
R3: 2k; R_0603_1608Metric
R4: 15k; R_0603_1608Metric
R_CC1, R_CC2: 5.1k; R_0402_1005Metric
TH1: NTC 10k; R_0603_1608Metric
U3: USBLC6-2SC6; SOT-23-6
U4: MCP73871; QFN-20-1EP_4x4mm_P0.5mm_EP2.5x2.5mm
U5: TPS63001DRCR; VREG_V62_16624-01YE
U6: TPS22919DCKT; SOT65P210X110-6N
U7: LC709203FQH-01TWG; WDFN-8-1EP_4x3mm_P0.65mm_EP2.4x1.8mm

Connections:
+3V3: C14.1, C15.1, U5.1 (VOUT), U5.7 (PS/SYNC), U5.10 (FB); also elsewhere on the board
I2C_SCL: U7.8 (SCL); also elsewhere on the board
I2C_SDA: U7.7 (SDA); also elsewhere on the board
unnamed: C_OUT1.1, U4.1 (OUT), U4.20 (OUT)
unnamed: C11.1, J1.1, U4.14 (V_{BAT}), U4.15 (V_{BAT}), U4.16 (V_{BAT_SENSE})
unnamed: J2.A5 (CC1), R_CC1.2
unnamed: J2.B5 (CC2), R_CC2.1
unnamed: J2.A7 (DN1), J2.B7 (DN2), U3.3 (I/O2)
unnamed: J2.A6 (DP1), J2.B6 (DP2), U3.1 (I/O1)
unnamed: R3.1, U4.13 (PROG1)
unnamed: R4.2, U4.12 (PROG3)
unnamed: TH1.2, U4.5 (THERM), U7.6 (T_{SENSE})
unnamed: L1.2, U5.4 (L1)
unnamed: L1.1, U5.2 (L2)
SA818_PD: U6.3 (ON); also elsewhere on the board
SA818_VCC: C17.1, C18.1, U6.6 (VOUT); also elsewhere on the board
USB_DM: U3.4 (I/O2); also elsewhere on the board
USB_DP: U3.6 (I/O1); also elsewhere on the board
VBUS: C10.1, C_USB1.2, D_VBUS1.2 (A2), J2.A4_B9 (VBUS), J2.B4_A9 (VBUS), U3.5 (VBUS), U4.2 (VPCC), U4.4 (PROG2), U4.9 (~TE), U4.17 (CE)
VSYS: C12.1, C13.2, C16.1, U5.5 (VIN), U5.6 (EN), U5.8 (VINA), U6.1 (IN), U7.3 (V_{DD})
